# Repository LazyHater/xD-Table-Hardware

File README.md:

# xD-Table-Hardware
Hardware of xD-Table

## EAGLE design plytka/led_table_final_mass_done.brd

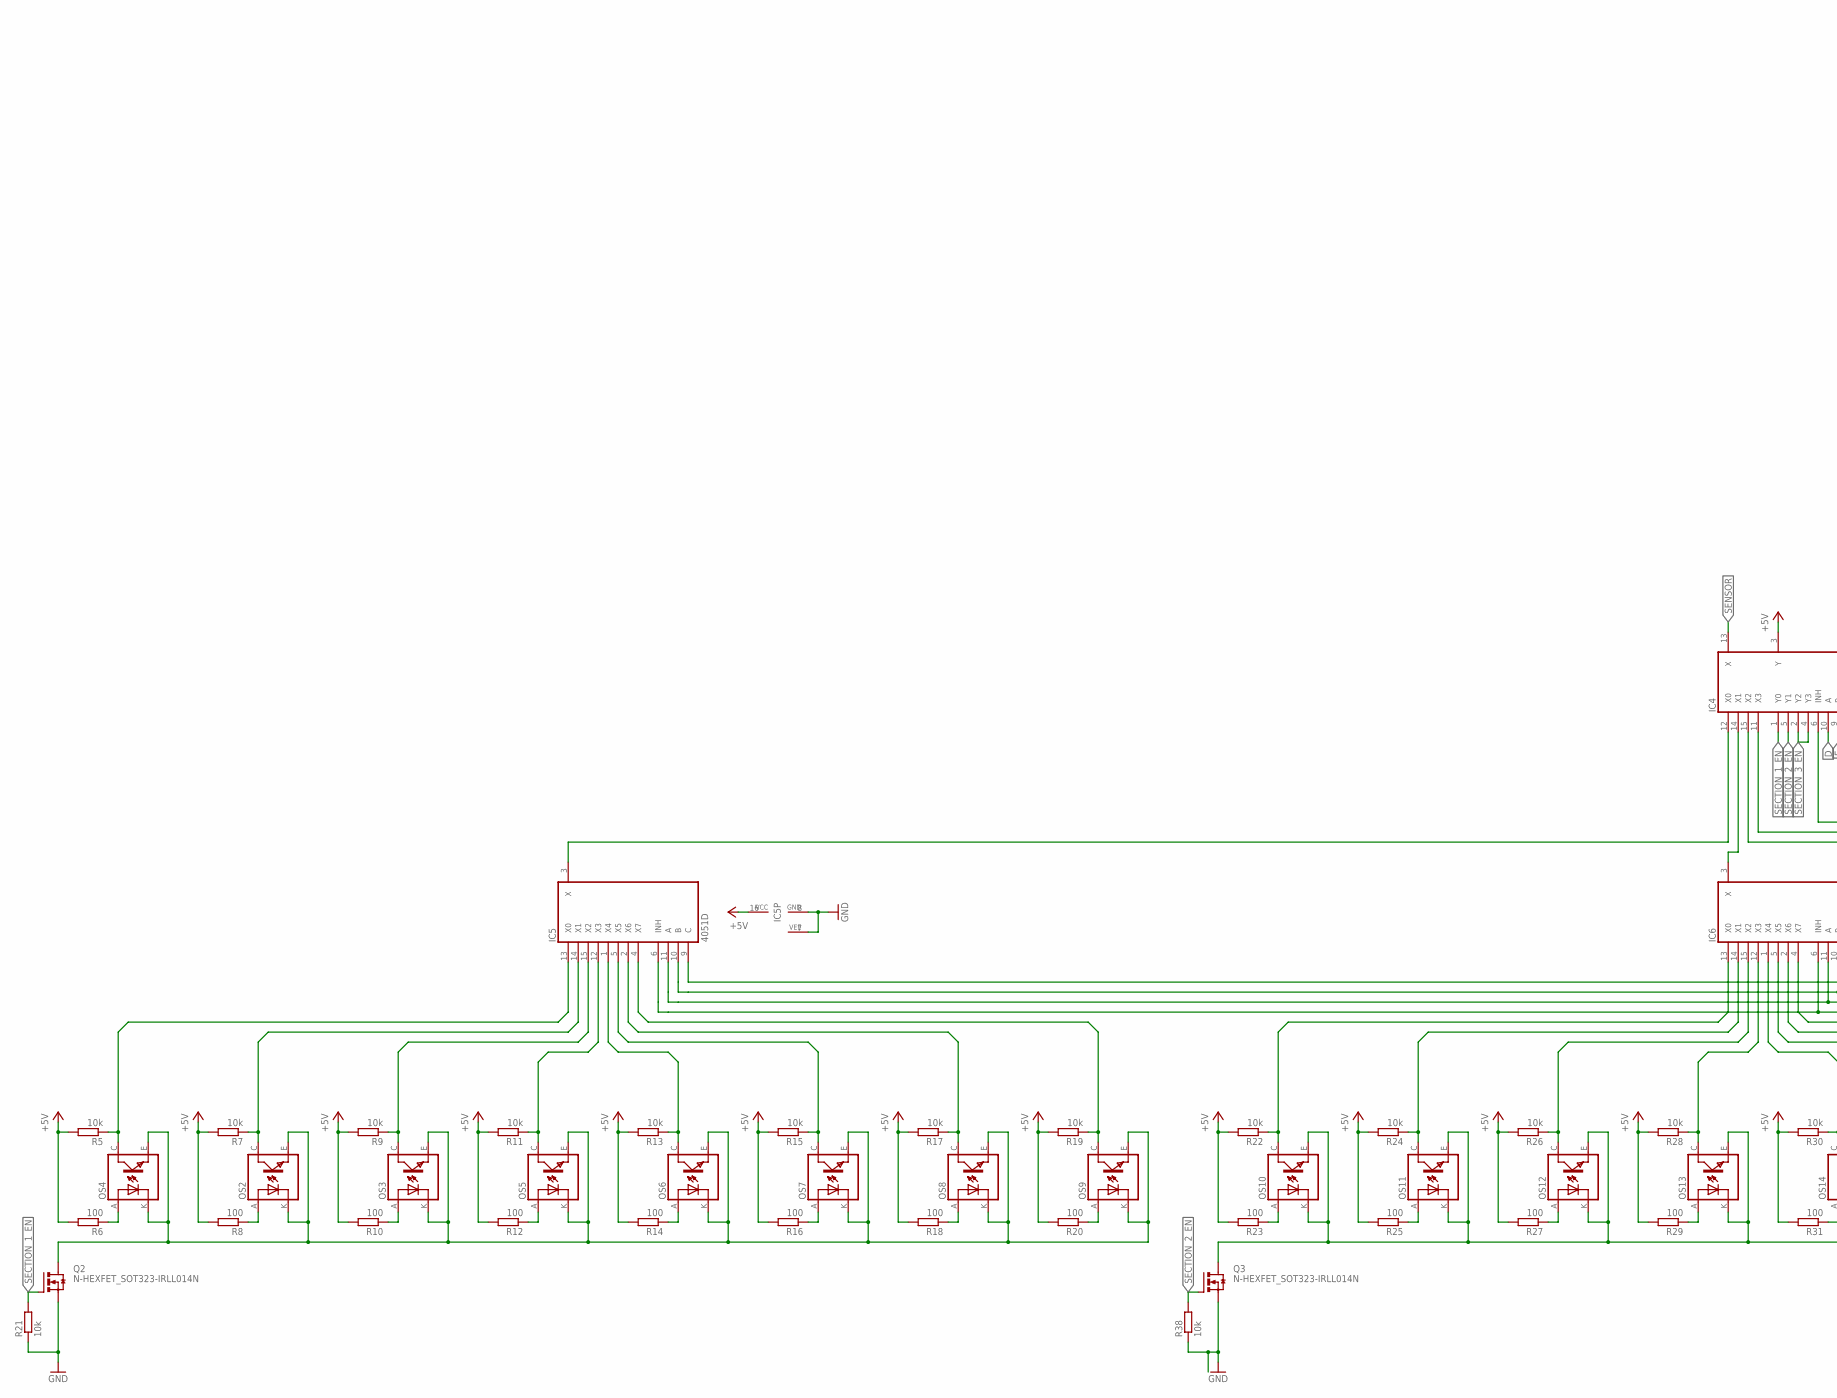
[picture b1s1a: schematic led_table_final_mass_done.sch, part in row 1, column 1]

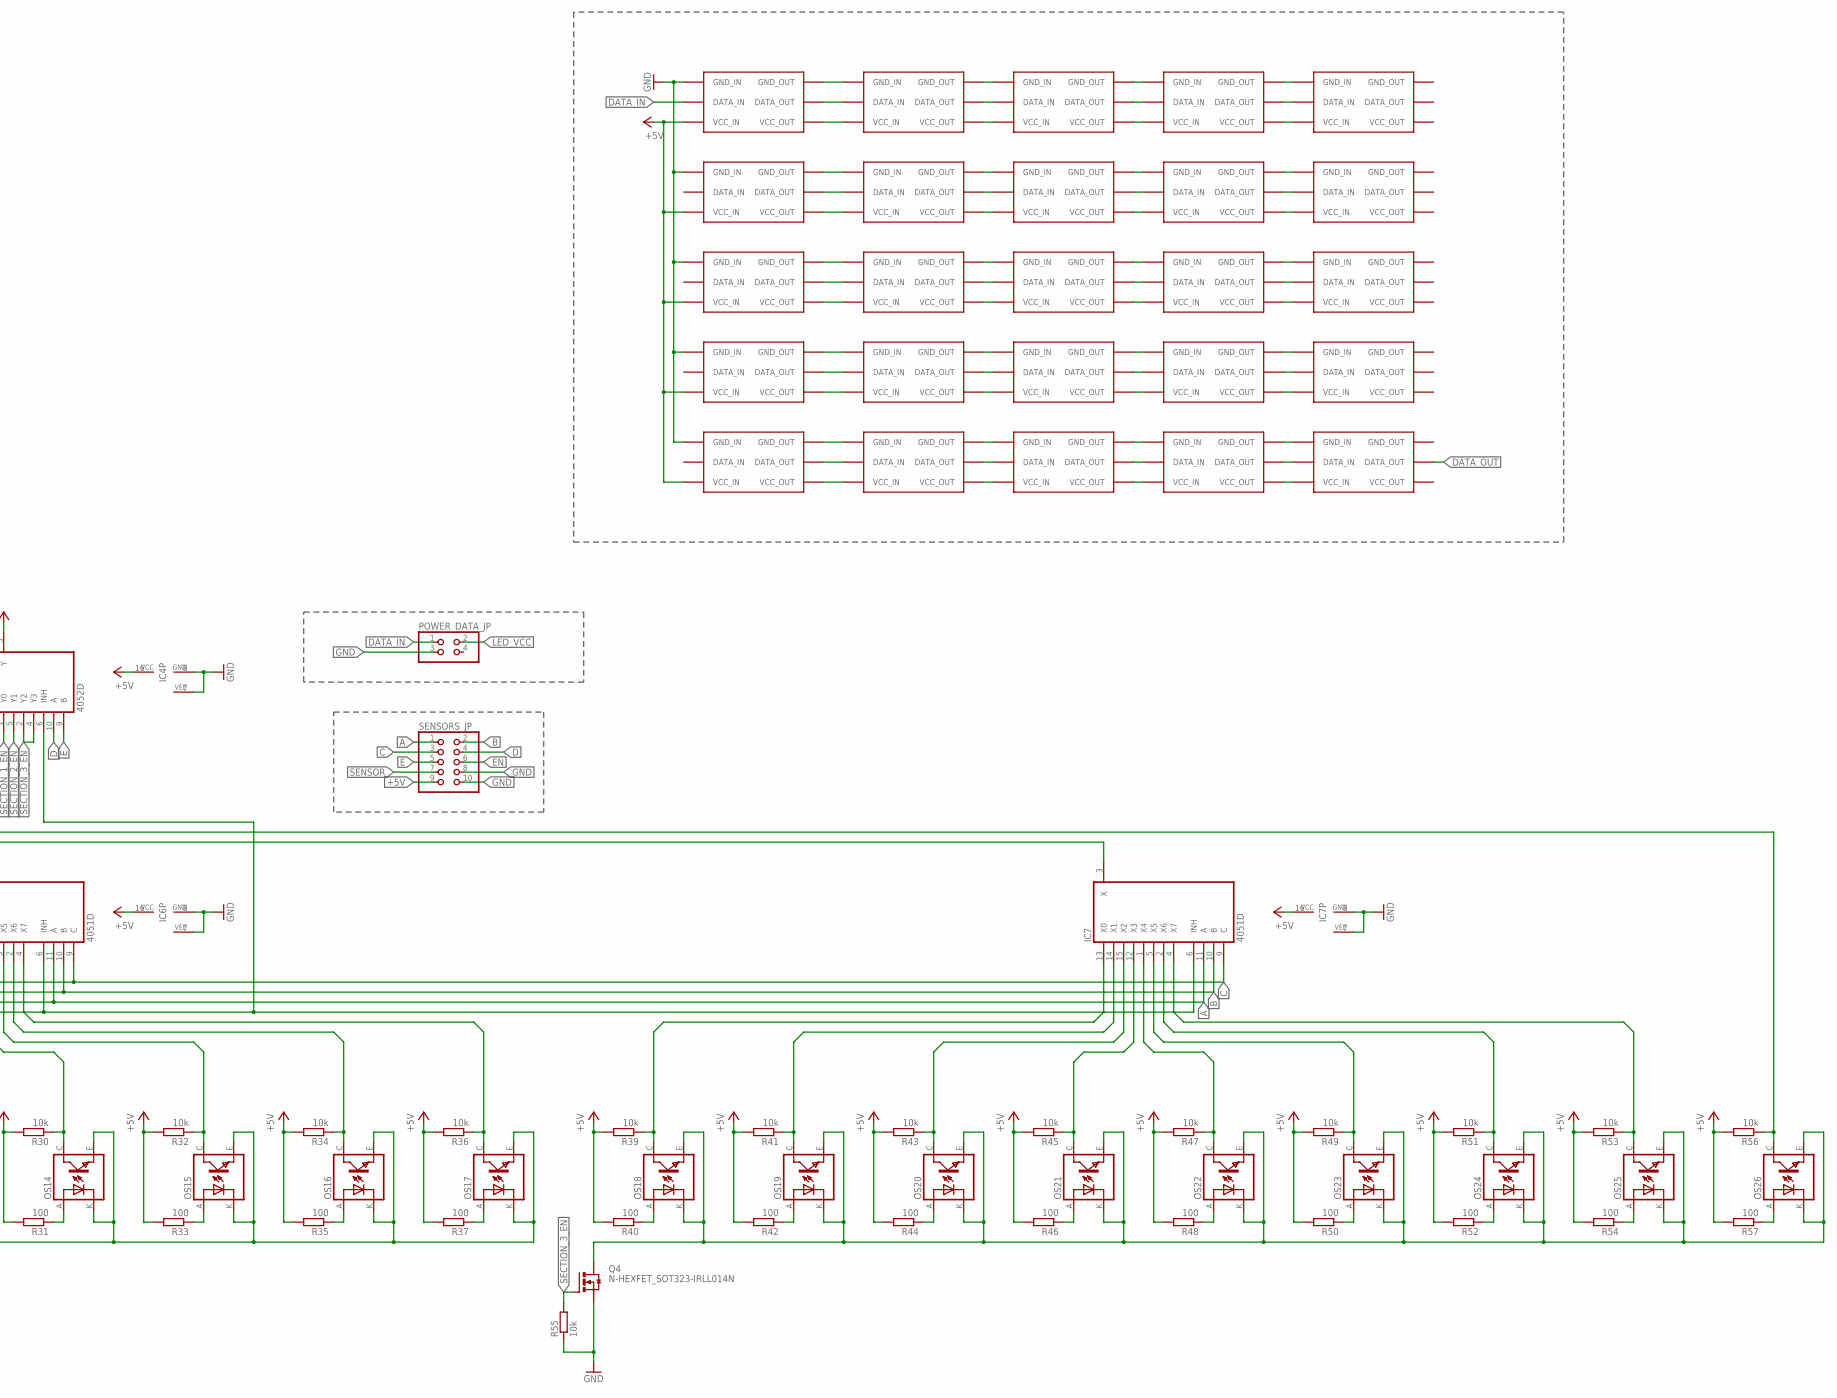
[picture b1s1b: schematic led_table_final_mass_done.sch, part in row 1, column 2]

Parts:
IC4: 4052D; SO16
IC5, IC6, IC7: 4051D; SO16
OS2, OS3, OS4, OS5, OS6, OS7, OS8, OS9, OS10, OS11, OS12, OS13, OS14, OS15, OS16, OS17, OS18, OS19, OS20, OS21, OS22, OS23, OS24, OS25, OS26: TCRT5000
POWER_DATA_JP: PINHD-2X2; 2X02
Q2, Q3, Q4: N-HEXFET_SOT323-IRLL014N; SOT223
R5, R7, R9, R11, R13, R15, R17, R19, R21, R22, R24, R26, R28, R30, R32, R34, R36, R38, R39, R41, R43, R45, R47, R49, R51, R53, R55, R56: 10k; R1206
R6, R8, R10, R12, R14, R16, R18, R20, R23, R25, R27, R29, R31, R33, R35, R37, R40, R42, R44, R46, R48, R50, R52, R54, R57: 100; R1206
SENSORS_JP: PINHD-2X5; 2X05
U$1, U$2, U$3, U$4, U$5, U$6, U$7, U$8, U$9, U$10, U$11, U$12, U$13, U$14, U$15, U$16, U$17, U$18, U$19, U$20, U$21, U$22, U$23, U$24, U$25: WS2812_ON_STRIP; WS_PIN

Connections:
+5V: IC4.3 (Y), IC4.16 (VCC), IC5.16 (VCC), IC6.16 (VCC), IC7.16 (VCC), R5.2, R6.2, R7.2, R8.2, R9.2, R10.2, R11.2, R12.2, R13.2, R14.2, R15.2, R16.2, R17.2, R18.2, R19.2, R20.2, R22.2, R23.2, R24.2, R25.2, R26.2, R27.2, R28.2, R29.2, R30.2, R31.2, R32.2, R33.2, R34.2, R35.2, R36.2, R37.2, R39.2, R40.2, R41.2, R42.2, R43.2, R44.2, R45.2, R46.2, R47.2, R48.2, R49.2, R50.2, R51.2, R52.2, R53.2, R54.2, R56.2, R57.2, SENSORS_JP.9
A: IC5.11 (A), IC6.11 (A), IC7.11 (A), SENSORS_JP.1
B: IC5.10 (B), IC6.10 (B), IC7.10 (B), SENSORS_JP.2
C: IC5.9 (C), IC6.9 (C), IC7.9 (C), SENSORS_JP.3
D: IC4.10 (A), SENSORS_JP.4
DATA_IN: POWER_DATA_JP.1, U$16.DATA_IN
DATA_OUT: U$10.DATA_OUT
E: IC4.9 (B), SENSORS_JP.5
EN: IC4.6 (INH), IC5.6 (INH), IC6.6 (INH), IC7.6 (INH), SENSORS_JP.6
GND: IC4.7 (VEE), IC4.8 (GND), IC5.7 (VEE), IC5.8 (GND), IC6.7 (VEE), IC6.8 (GND), IC7.7 (VEE), IC7.8 (GND), POWER_DATA_JP.3, Q2.3 (S), Q3.3 (S), Q4.3 (S), R21.1, R38.1, R55.1, SENSORS_JP.8, SENSORS_JP.10, U$1.GND_IN, U$6.GND_IN, U$11.GND_IN, U$16.GND_IN, U$21.GND_IN
GND_OUT: U$5.GND_OUT, U$10.GND_OUT, U$15.GND_OUT, U$20.GND_OUT, U$25.GND_OUT
LED_VCC: POWER_DATA_JP.2, U$1.VCC_IN, U$6.VCC_IN, U$11.VCC_IN, U$16.VCC_IN, U$21.VCC_IN
unnamed: U$1.VCC_OUT, U$2.VCC_IN
unnamed: U$1.DATA_OUT, U$2.DATA_IN
unnamed: U$1.GND_OUT, U$2.GND_IN
unnamed: U$2.VCC_OUT, U$3.VCC_IN
unnamed: U$2.DATA_OUT, U$3.DATA_IN
unnamed: U$2.GND_OUT, U$3.GND_IN
unnamed: U$3.VCC_OUT, U$4.VCC_IN
unnamed: U$3.DATA_OUT, U$4.DATA_IN
unnamed: U$3.GND_OUT, U$4.GND_IN
unnamed: U$4.VCC_OUT, U$5.VCC_IN
unnamed: OS4.A (ANODE), R6.1
unnamed: IC5.13 (X0), OS4.C (COLLECTOR), R5.1
unnamed: IC5.14 (X1), OS2.C (COLLECTOR), R7.1
unnamed: IC5.15 (X2), OS3.C (COLLECTOR), R9.1
unnamed: OS2.A (ANODE), R8.1
unnamed: IC5.1 (X4), OS6.C (COLLECTOR), R13.1
unnamed: IC6.13 (X0), OS10.C (COLLECTOR), R22.1
unnamed: OS3.A (ANODE), R10.1
unnamed: OS10.A (ANODE), R23.1
unnamed: IC5.12 (X3), OS5.C (COLLECTOR), R11.1
unnamed: OS5.A (ANODE), R12.1
unnamed: IC6.14 (X1), OS11.C (COLLECTOR), R24.1
unnamed: OS11.A (ANODE), R25.1
unnamed: OS6.A (ANODE), R14.1
unnamed: OS12.A (ANODE), R27.1
unnamed: IC5.5 (X5), OS7.C (COLLECTOR), R15.1
unnamed: OS7.A (ANODE), R16.1
unnamed: IC6.12 (X3), OS13.C (COLLECTOR), R28.1
unnamed: IC5.2 (X6), OS8.C (COLLECTOR), R17.1
unnamed: OS8.A (ANODE), R18.1
unnamed: OS2.E (EMITTER), OS2.K (CATHODE), OS3.E (EMITTER), OS3.K (CATHODE), OS4.E (EMITTER), OS4.K (CATHODE), OS5.E (EMITTER), OS5.K (CATHODE), OS6.E (EMITTER), OS6.K (CATHODE), OS7.E (EMITTER), OS7.K (CATHODE), OS8.E (EMITTER), OS8.K (CATHODE), OS9.E (EMITTER), OS9.K (CATHODE), Q2.4 (D)
unnamed: IC5.4 (X7), OS9.C (COLLECTOR), R19.1
unnamed: OS9.A (ANODE), R20.1
unnamed: OS13.A (ANODE), R29.1
unnamed: U$4.DATA_OUT, U$5.DATA_IN
unnamed: OS14.A (ANODE), R31.1
unnamed: IC6.5 (X5), OS15.C (COLLECTOR), R32.1
unnamed: OS15.A (ANODE), R33.1
unnamed: IC6.2 (X6), OS16.C (COLLECTOR), R34.1
unnamed: OS16.A (ANODE), R35.1
unnamed: OS10.E (EMITTER), OS10.K (CATHODE), OS11.E (EMITTER), OS11.K (CATHODE), OS12.E (EMITTER), OS12.K (CATHODE), OS13.E (EMITTER), OS13.K (CATHODE), OS14.E (EMITTER), OS14.K (CATHODE), OS15.E (EMITTER), OS15.K (CATHODE), OS16.E (EMITTER), OS16.K (CATHODE), OS17.E (EMITTER), OS17.K (CATHODE), Q3.4 (D)
unnamed: IC6.4 (X7), OS17.C (COLLECTOR), R36.1
unnamed: OS17.A (ANODE), R37.1
unnamed: U$4.GND_OUT, U$5.GND_IN
unnamed: IC6.15 (X2), OS12.C (COLLECTOR), R26.1
unnamed: IC6.1 (X4), OS14.C (COLLECTOR), R30.1
unnamed: IC7.13 (X0), OS18.C (COLLECTOR), R39.1
unnamed: OS18.A (ANODE), R40.1
unnamed: IC7.14 (X1), OS19.C (COLLECTOR), R41.1
unnamed: OS19.A (ANODE), R42.1
unnamed: OS20.A (ANODE), R44.1
unnamed: IC7.12 (X3), OS21.C (COLLECTOR), R45.1
unnamed: OS21.A (ANODE), R46.1
unnamed: OS22.A (ANODE), R48.1
unnamed: IC7.5 (X5), OS23.C (COLLECTOR), R49.1
unnamed: OS23.A (ANODE), R50.1
unnamed: IC7.2 (X6), OS24.C (COLLECTOR), R51.1
unnamed: OS24.A (ANODE), R52.1
unnamed: U$6.VCC_OUT, U$7.VCC_IN
unnamed: IC7.4 (X7), OS25.C (COLLECTOR), R53.1
unnamed: OS25.A (ANODE), R54.1
unnamed: U$6.DATA_OUT, U$7.DATA_IN
unnamed: IC7.15 (X2), OS20.C (COLLECTOR), R43.1
unnamed: IC7.1 (X4), OS22.C (COLLECTOR), R47.1
unnamed: U$6.GND_OUT, U$7.GND_IN
unnamed: U$7.VCC_OUT, U$8.VCC_IN
unnamed: U$7.DATA_OUT, U$8.DATA_IN
unnamed: U$7.GND_OUT, U$8.GND_IN
unnamed: IC4.12 (X0), IC5.3 (X)
unnamed: IC4.14 (X1), IC6.3 (X)
unnamed: IC4.15 (X2), IC7.3 (X)
unnamed: IC4.11 (X3), OS26.C (COLLECTOR), R56.1
unnamed: OS18.E (EMITTER), OS18.K (CATHODE), OS19.E (EMITTER), OS19.K (CATHODE), OS20.E (EMITTER), OS20.K (CATHODE), OS21.E (EMITTER), OS21.K (CATHODE), OS22.E (EMITTER), OS22.K (CATHODE), OS23.E (EMITTER), OS23.K (CATHODE), OS24.E (EMITTER), OS24.K (CATHODE), OS25.E (EMITTER), OS25.K (CATHODE), OS26.E (EMITTER), OS26.K (CATHODE), Q4.4 (D)
unnamed: U$8.VCC_OUT, U$9.VCC_IN
unnamed: OS26.A (ANODE), R57.1
unnamed: U$8.DATA_OUT, U$9.DATA_IN
unnamed: U$8.GND_OUT, U$9.GND_IN
unnamed: U$9.VCC_OUT, U$10.VCC_IN
unnamed: U$9.DATA_OUT, U$10.DATA_IN
unnamed: U$9.GND_OUT, U$10.GND_IN
unnamed: U$11.VCC_OUT, U$12.VCC_IN
unnamed: U$11.DATA_OUT, U$12.DATA_IN
unnamed: U$11.GND_OUT, U$12.GND_IN
unnamed: U$12.VCC_OUT, U$13.VCC_IN
unnamed: U$12.DATA_OUT, U$13.DATA_IN
unnamed: U$12.GND_OUT, U$13.GND_IN
unnamed: U$13.VCC_OUT, U$14.VCC_IN
unnamed: U$13.DATA_OUT, U$14.DATA_IN
unnamed: U$13.GND_OUT, U$14.GND_IN
unnamed: U$14.VCC_OUT, U$15.VCC_IN
unnamed: U$14.DATA_OUT, U$15.DATA_IN
unnamed: U$14.GND_OUT, U$15.GND_IN
unnamed: U$16.VCC_OUT, U$17.VCC_IN
unnamed: U$16.DATA_OUT, U$17.DATA_IN
unnamed: U$16.GND_OUT, U$17.GND_IN
unnamed: U$17.VCC_OUT, U$18.VCC_IN
unnamed: U$17.DATA_OUT, U$18.DATA_IN
unnamed: U$17.GND_OUT, U$18.GND_IN
unnamed: U$18.VCC_OUT, U$19.VCC_IN
unnamed: U$18.DATA_OUT, U$19.DATA_IN
unnamed: U$18.GND_OUT, U$19.GND_IN
unnamed: U$19.VCC_OUT, U$20.VCC_IN
unnamed: U$19.DATA_OUT, U$20.DATA_IN
unnamed: U$19.GND_OUT, U$20.GND_IN
unnamed: U$21.VCC_OUT, U$22.VCC_IN
unnamed: U$21.DATA_OUT, U$22.DATA_IN
unnamed: U$21.GND_OUT, U$22.GND_IN
unnamed: U$22.VCC_OUT, U$23.VCC_IN
unnamed: U$22.DATA_OUT, U$23.DATA_IN
unnamed: U$22.GND_OUT, U$23.GND_IN
unnamed: U$23.VCC_OUT, U$24.VCC_IN
unnamed: U$23.DATA_OUT, U$24.DATA_IN
unnamed: U$23.GND_OUT, U$24.GND_IN
unnamed: U$24.VCC_OUT, U$25.VCC_IN
unnamed: U$24.DATA_OUT, U$25.DATA_IN
unnamed: U$24.GND_OUT, U$25.GND_IN
SECTION_1_EN: IC4.1 (Y0), Q2.1 (G), R21.2
SECTION_2_EN: IC4.5 (Y1), Q3.1 (G), R38.2
SECTION_3_EN: IC4.2 (Y2), IC4.4 (Y3), Q4.1 (G), R55.2
SENSOR: IC4.13 (X), SENSORS_JP.7
VCC_OUT: U$5.VCC_OUT, U$10.VCC_OUT, U$15.VCC_OUT, U$20.VCC_OUT, U$25.VCC_OUT

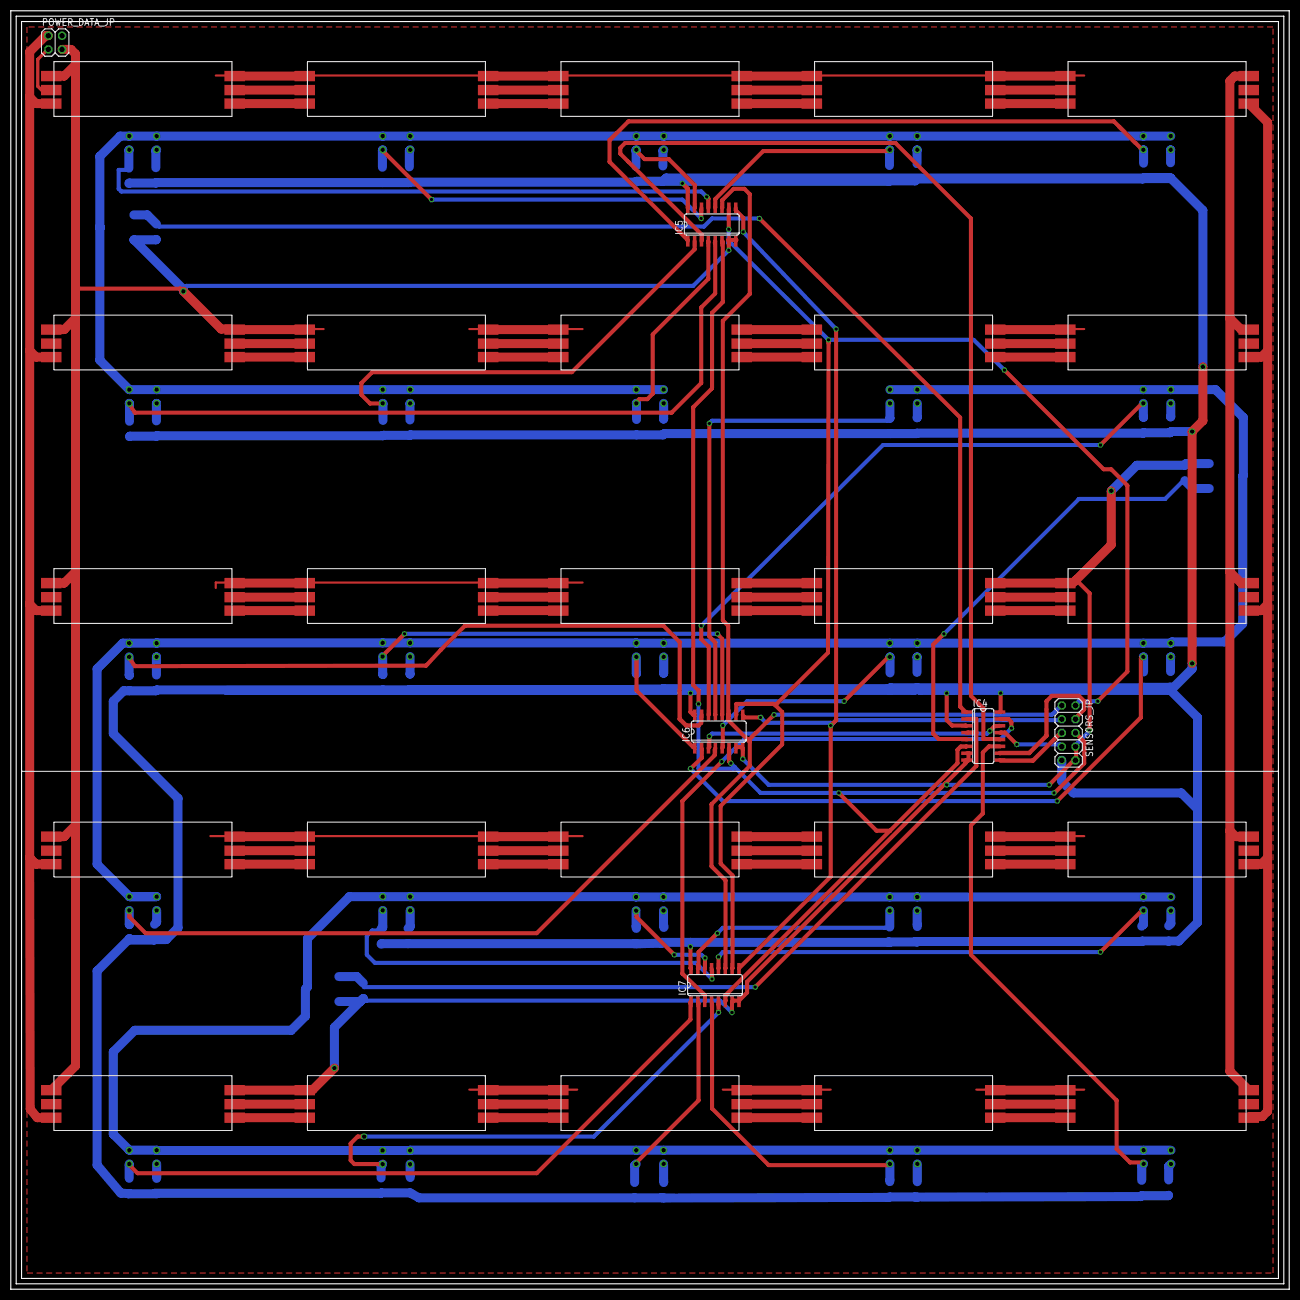
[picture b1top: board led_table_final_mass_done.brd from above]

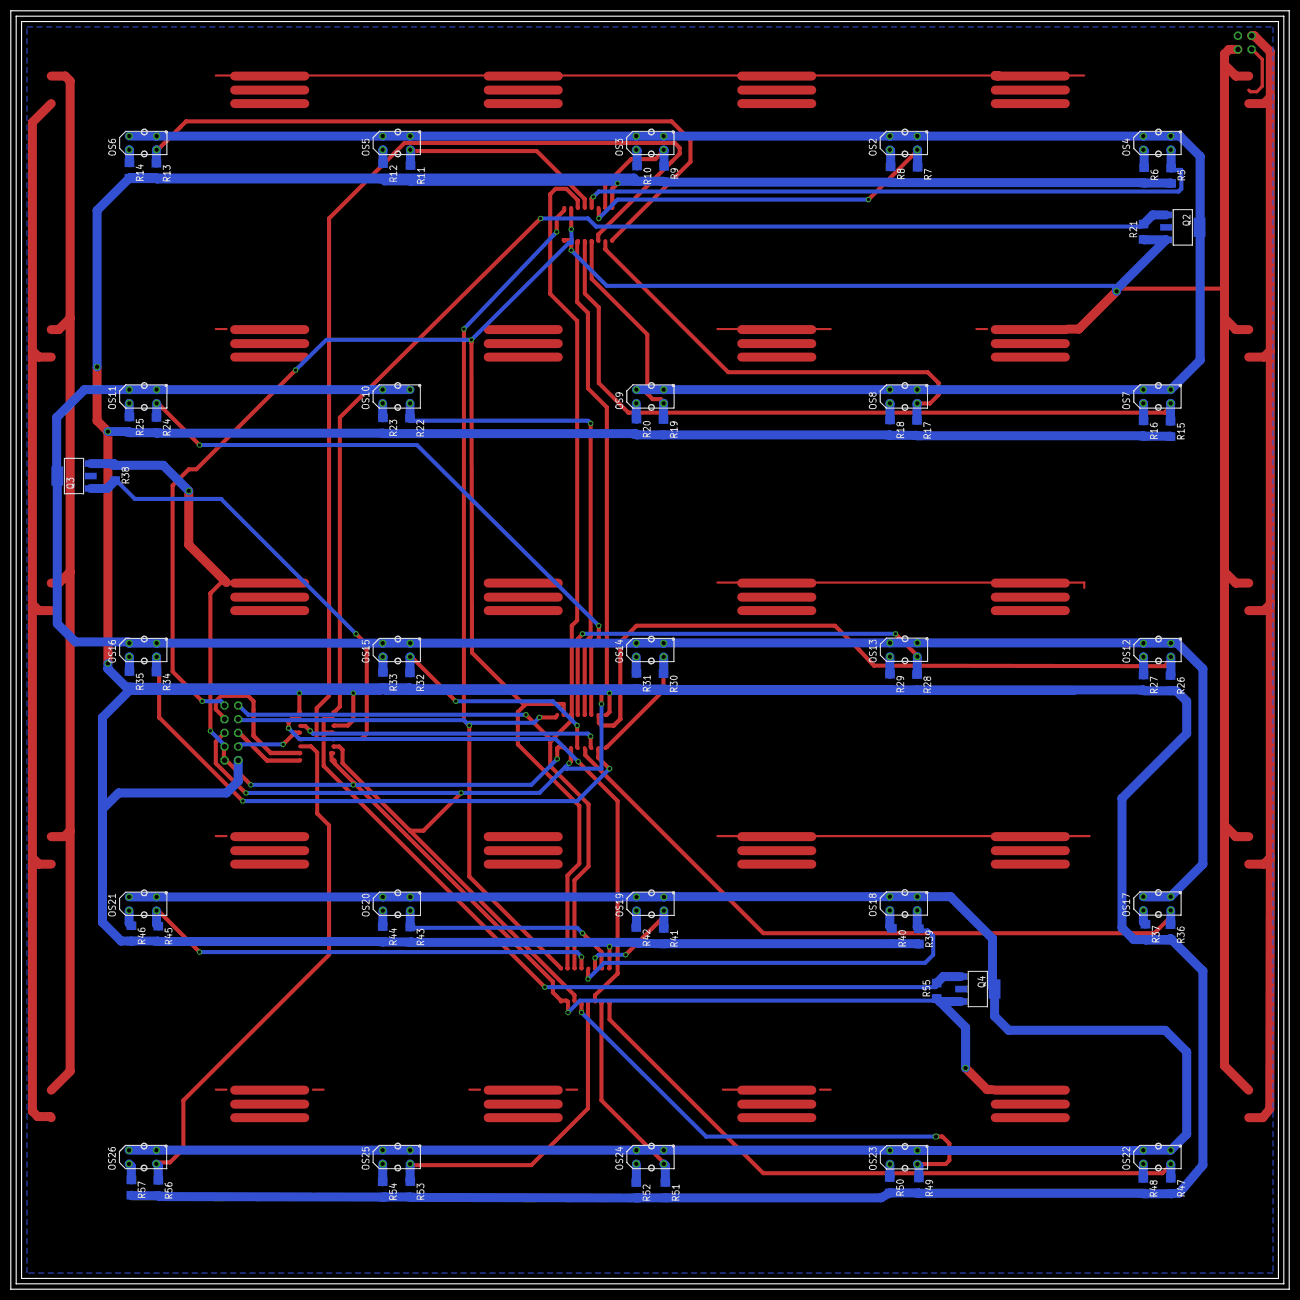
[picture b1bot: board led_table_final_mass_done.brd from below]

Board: 2 copper layers, 237.0 x 237.0 mm, 112 parts (81 on the bottom side), 132 nets.

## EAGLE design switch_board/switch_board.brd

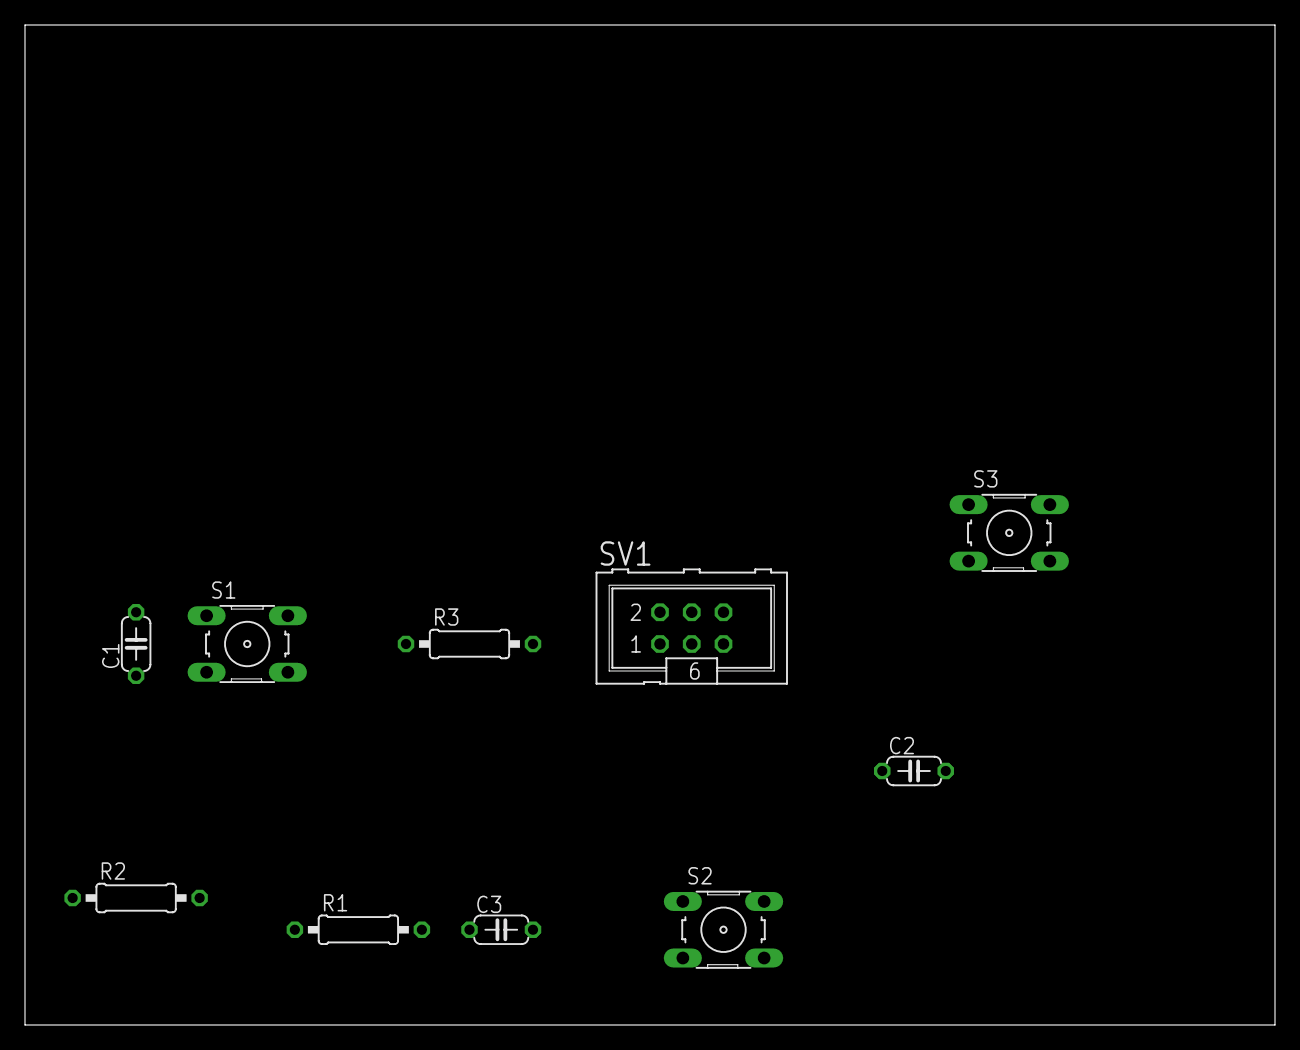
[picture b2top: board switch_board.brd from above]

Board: 2 copper layers, 100.0 x 80.0 mm, 10 parts (0 on the bottom side), 5 nets, no tracks yet.

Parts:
C1, C2, C3: 100nF; C050-024X044
R1, R2, R3: 47k; 0207/10
S1, S2, S3: B3F-10XX
SV1: ML6

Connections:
+3V3: R1.1, R2.1, R3.1, SV1.5
BTN1: C1.2, R1.2, S1.1, SV1.2
BTN2: C2.2, R2.2, S2.1, SV1.3
GND: C1.1, C2.1, C3.1, S1.3, S2.3, S3.3, SV1.6
RST_BTN: C3.2, R3.2, S3.1, SV1.1

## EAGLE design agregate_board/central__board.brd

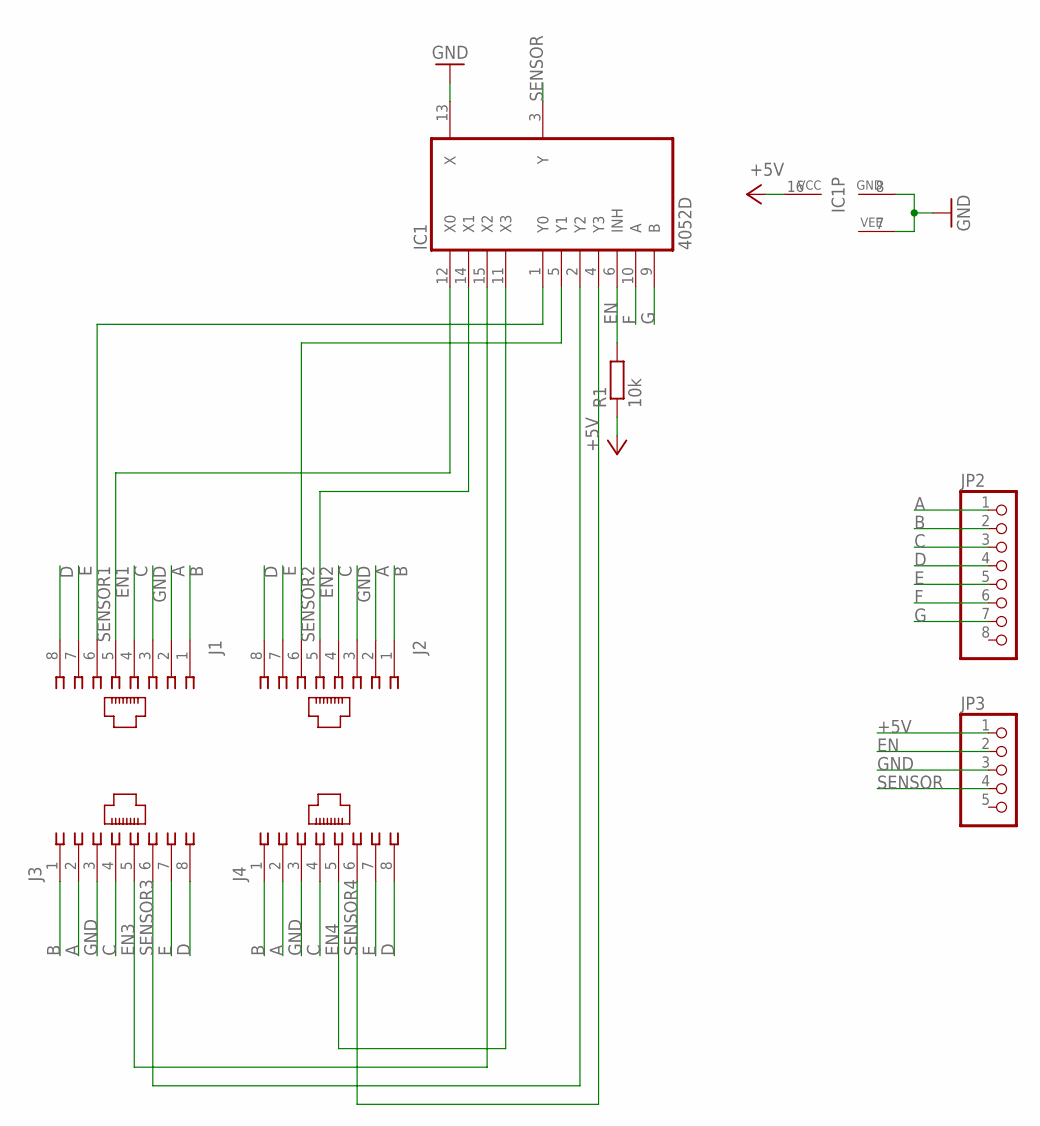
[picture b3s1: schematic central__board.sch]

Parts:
IC1: 4052D; SO16
J1, J2, J3, J4: 556416-1
JP2: PINHD-1X8; 1X08
JP3: PINHD-1X5; 1X05
R1: 10k; M1206

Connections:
+5V: IC1.16 (VCC), JP3.1, R1.1
A: J1.2, J2.2, J3.2, J4.2, JP2.1
B: J1.1, J2.1, J3.1, J4.1, JP2.2
C: J1.4, J2.4, J3.4, J4.4, JP2.3
D: J1.8, J2.8, J3.8, J4.8, JP2.4
E: J1.7, J2.7, J3.7, J4.7, JP2.5
EN: IC1.6 (INH), JP3.2, R1.2
EN1: IC1.12 (X0), J1.5
EN2: IC1.14 (X1), J2.5
EN3: IC1.15 (X2), J3.5
EN4: IC1.11 (X3), J4.5
F: IC1.10 (A), JP2.6
G: IC1.9 (B), JP2.7
GND: IC1.7 (VEE), IC1.8 (GND), IC1.13 (X), J1.3, J2.3, J3.3, J4.3, JP3.3
SENSOR: IC1.3 (Y), JP3.4
SENSOR1: IC1.1 (Y0), J1.6
SENSOR2: IC1.5 (Y1), J2.6
SENSOR3: IC1.2 (Y2), J3.6
SENSOR4: IC1.4 (Y3), J4.6

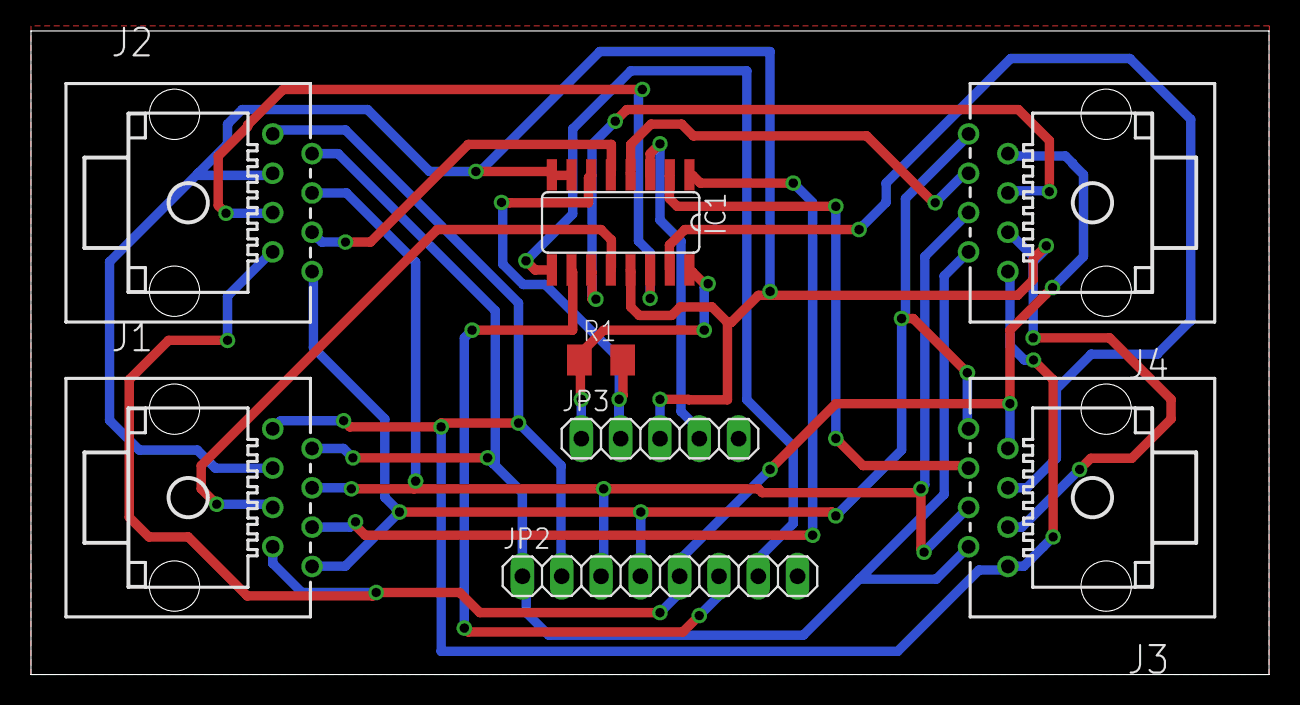
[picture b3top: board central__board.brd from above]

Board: 2 copper layers, 80.0 x 41.6 mm, 8 parts (0 on the bottom side), 19 nets.

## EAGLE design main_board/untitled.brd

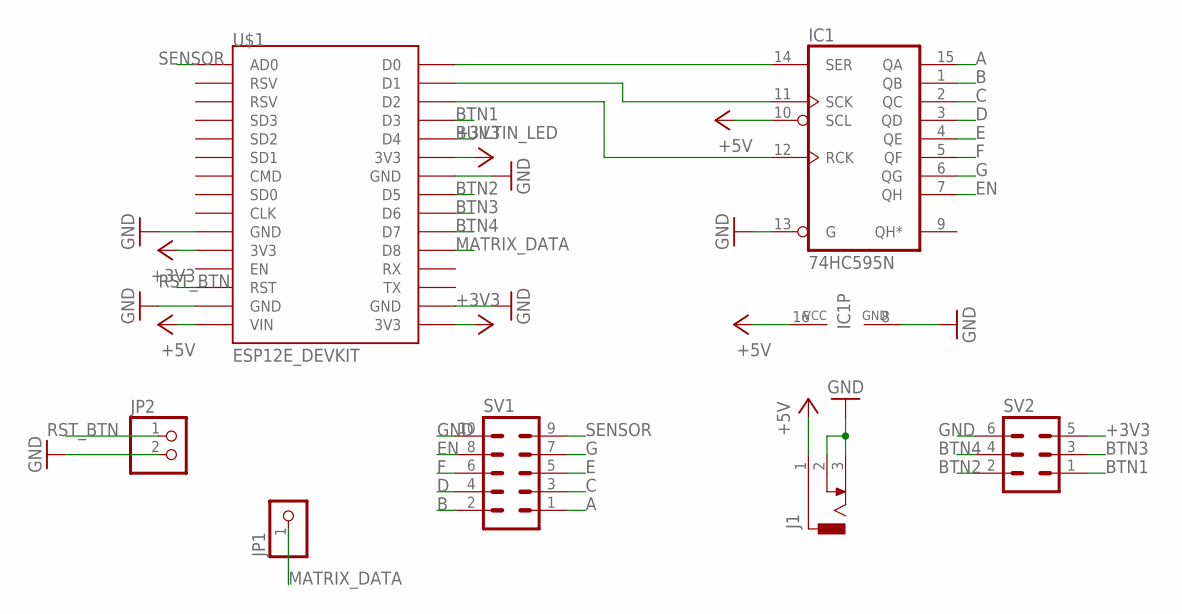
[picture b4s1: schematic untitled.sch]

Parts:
IC1: 74HC595N; DIL16
J1: DCJ0303
JP1: PINHD-1X1; 1X01
JP2: PINHD-1X2; 1X02
SV1: ML10
SV2: ML6
U$1: ESP12E_DEVKIT

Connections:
+3V3: SV2.5, U$1.3V3@0 (3V3), U$1.3V3@1 (3V3), U$1.3V3@2 (3V3)
+5V: IC1.10 (SCL), IC1.16 (VCC), J1.1, U$1.VIN
A: IC1.15 (QA), SV1.1
B: IC1.1 (QB), SV1.2
BTN1: SV2.1, U$1.D3
BTN2: SV2.2, U$1.D5
BTN3: SV2.3, U$1.D6
BTN4: SV2.4, U$1.D7
BUILTIN_LED: U$1.D4
C: IC1.2 (QC), SV1.3
D: IC1.3 (QD), SV1.4
E: IC1.4 (QE), SV1.5
EN: IC1.7 (QH), SV1.8
F: IC1.5 (QF), SV1.6
G: IC1.6 (QG), SV1.7
GND: IC1.8 (GND), IC1.13 (G), J1.2, J1.3, JP2.2, SV1.10, SV2.6, U$1.GND@0 (GND), U$1.GND@1 (GND), U$1.GND@2 (GND), U$1.GND@3 (GND)
MATRIX_DATA: JP1.1, U$1.D8
unnamed: IC1.14 (SER), U$1.D0
unnamed: IC1.11 (SCK), U$1.D1
unnamed: IC1.12 (RCK), U$1.D2
RST_BTN: JP2.1, U$1.RST
SENSOR: SV1.9, U$1.AD0

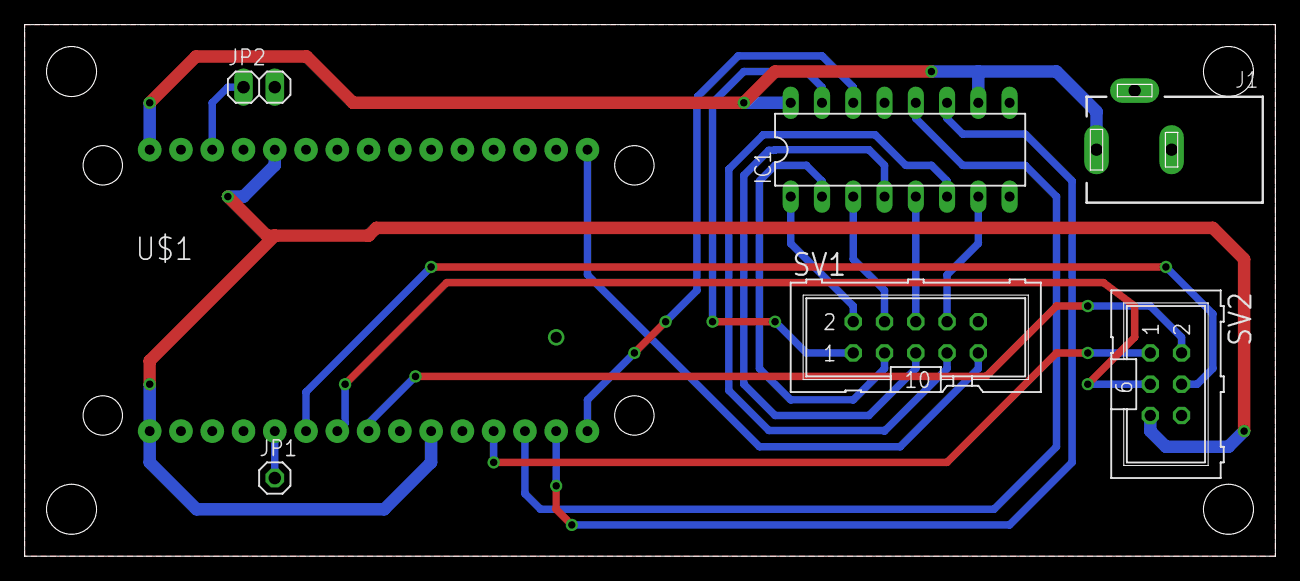
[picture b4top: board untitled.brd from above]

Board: 2 copper layers, 101.6 x 43.2 mm, 7 parts (0 on the bottom side), 21 nets.
